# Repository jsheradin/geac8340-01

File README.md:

# geac8340-01
Modernization project for a library terminal keyboard

The libararies are not my own, I just referenced them. Only footprints I added are Stackpole and mounting holes.

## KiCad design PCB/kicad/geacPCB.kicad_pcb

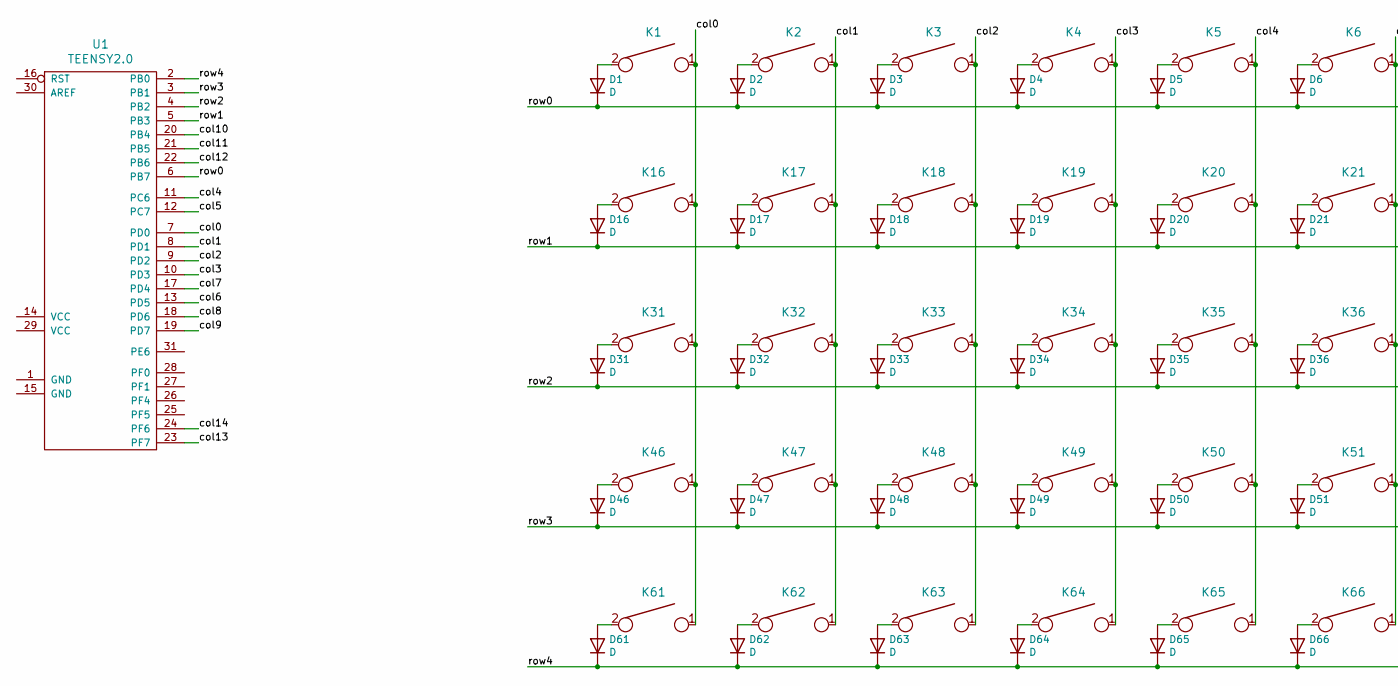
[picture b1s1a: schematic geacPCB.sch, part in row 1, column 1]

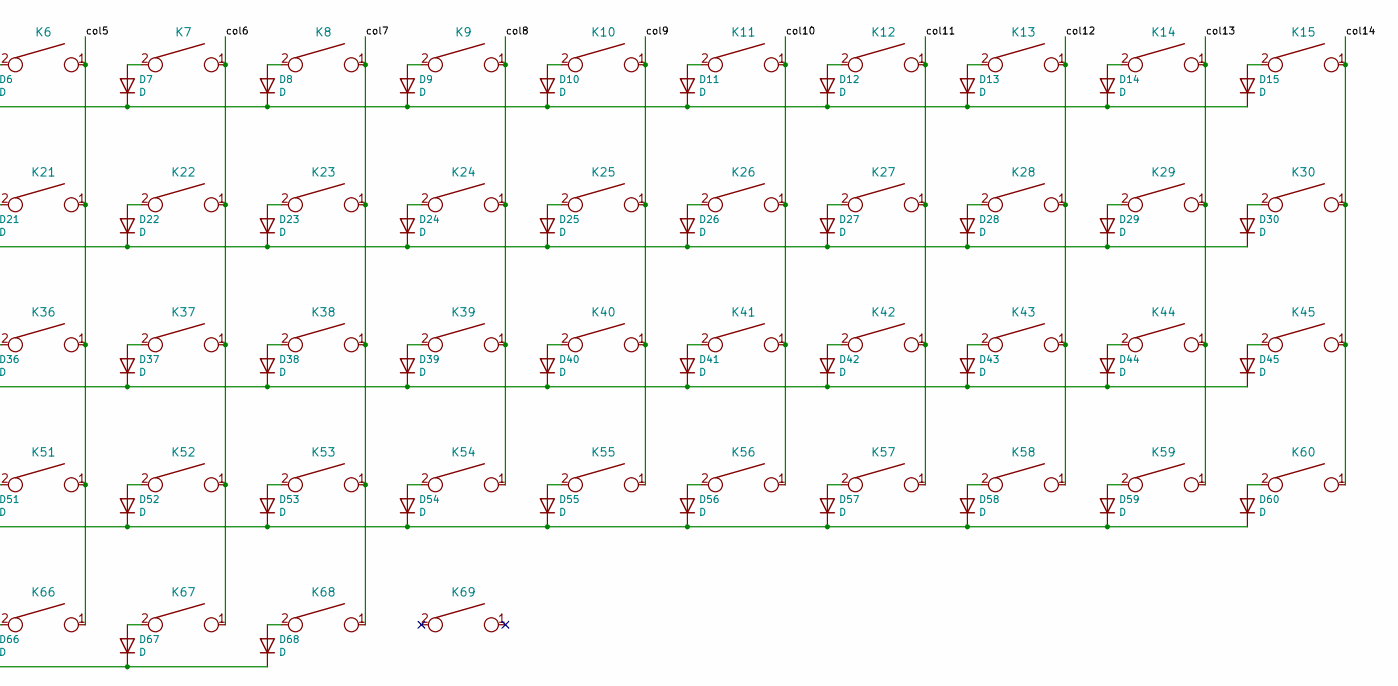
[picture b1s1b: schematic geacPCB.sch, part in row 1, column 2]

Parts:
D1, D2, D3, D4, D5, D6, D7, D8, D9, D10, D11, D12, D13, D14, D15, D16, D17, D18, D19, D20, D21, D22, D23, D24, D25, D26, D27, D28, D29, D30, D31, D32, D33, D34, D35, D36, D37, D38, D39, D40, D41, D42, D43, D44, D45, D46, D47, D48, D49, D50, D51, D52, D53, D54, D55, D56, D57, D58, D59, D60, D61, D62, D63, D64, D65, D66, D67, D68: D; D_SOD123_axial
K1, K2, K3, K4, K5, K6, K7, K8, K9, K10, K11, K12, K13, K14, K15, K16, K17, K18, K19, K20, K21, K22, K23, K24, K25, K26, K27, K28, K29, K30, K31, K32, K33, K34, K35, K36, K37, K38, K39, K40, K41, K42, K43, K44, K45, K46, K47, K48, K49, K50, K51, K52, K53, K54, K55, K56, K57, K58, K59, K60, K61, K62, K63, K64, K65, K66, K67, K68, K69: KEYSW; Stackpole
U1: TEENSY2.0; Teensy2.0

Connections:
/col0: K1.1, K16.1, K31.1, K46.1, K61.1, U1.7 (PD0)
/col1: K2.1, K17.1, K32.1, K47.1, K62.1, U1.8 (PD1)
/col2: K3.1, K18.1, K33.1, K48.1, K63.1, U1.9 (PD2)
/col3: K4.1, K19.1, K34.1, K49.1, K64.1, U1.10 (PD3)
/col4: K5.1, K20.1, K35.1, K50.1, K65.1, U1.11 (PC6)
/col5: K6.1, K21.1, K36.1, K51.1, K66.1, U1.12 (PC7)
/col6: K7.1, K22.1, K37.1, K52.1, K67.1, U1.13 (PD5)
/col7: K8.1, K23.1, K38.1, K53.1, K68.1, U1.17 (PD4)
/col8: K9.1, K24.1, K39.1, K54.1, U1.18 (PD6)
/col9: K10.1, K25.1, K40.1, K55.1, U1.19 (PD7)
/col10: K11.1, K26.1, K41.1, K56.1, U1.20 (PB4)
/col11: K12.1, K27.1, K42.1, K57.1, U1.21 (PB5)
/col12: K13.1, K28.1, K43.1, K58.1, U1.22 (PB6)
/col13: K14.1, K29.1, K44.1, K59.1, U1.23 (PF7)
/col14: K15.1, K30.1, K45.1, K60.1, U1.24 (PF6)
/row0: D1.1 (K), D2.1 (K), D3.1 (K), D4.1 (K), D5.1 (K), D6.1 (K), D7.1 (K), D8.1 (K), D9.1 (K), D10.1 (K), D11.1 (K), D12.1 (K), D13.1 (K), D14.1 (K), D15.1 (K), U1.6 (PB7)
/row1: D16.1 (K), D17.1 (K), D18.1 (K), D19.1 (K), D20.1 (K), D21.1 (K), D22.1 (K), D23.1 (K), D24.1 (K), D25.1 (K), D26.1 (K), D27.1 (K), D28.1 (K), D29.1 (K), D30.1 (K), U1.5 (PB3)
/row2: D31.1 (K), D32.1 (K), D33.1 (K), D34.1 (K), D35.1 (K), D36.1 (K), D37.1 (K), D38.1 (K), D39.1 (K), D40.1 (K), D41.1 (K), D42.1 (K), D43.1 (K), D44.1 (K), D45.1 (K), U1.4 (PB2)
/row3: D46.1 (K), D47.1 (K), D48.1 (K), D49.1 (K), D50.1 (K), D51.1 (K), D52.1 (K), D53.1 (K), D54.1 (K), D55.1 (K), D56.1 (K), D57.1 (K), D58.1 (K), D59.1 (K), D60.1 (K), U1.3 (PB1)
/row4: D61.1 (K), D62.1 (K), D63.1 (K), D64.1 (K), D65.1 (K), D66.1 (K), D67.1 (K), D68.1 (K), U1.2 (PB0)
unnamed: D1.2 (A), K1.2
unnamed: D2.2 (A), K2.2
unnamed: D3.2 (A), K3.2
unnamed: D4.2 (A), K4.2
unnamed: D5.2 (A), K5.2
unnamed: D6.2 (A), K6.2
unnamed: D7.2 (A), K7.2
unnamed: D8.2 (A), K8.2
unnamed: D9.2 (A), K9.2
unnamed: D10.2 (A), K10.2
unnamed: D11.2 (A), K11.2
unnamed: D12.2 (A), K12.2
unnamed: D13.2 (A), K13.2
unnamed: D14.2 (A), K14.2
unnamed: D15.2 (A), K15.2
unnamed: D16.2 (A), K16.2
unnamed: D17.2 (A), K17.2
unnamed: D18.2 (A), K18.2
unnamed: D19.2 (A), K19.2
unnamed: D20.2 (A), K20.2
unnamed: D21.2 (A), K21.2
unnamed: D22.2 (A), K22.2
unnamed: D23.2 (A), K23.2
unnamed: D24.2 (A), K24.2
unnamed: D25.2 (A), K25.2
unnamed: D26.2 (A), K26.2
unnamed: D27.2 (A), K27.2
unnamed: D28.2 (A), K28.2
unnamed: D29.2 (A), K29.2
unnamed: D30.2 (A), K30.2
unnamed: D31.2 (A), K31.2
unnamed: D32.2 (A), K32.2
unnamed: D33.2 (A), K33.2
unnamed: D34.2 (A), K34.2
unnamed: D35.2 (A), K35.2
unnamed: D36.2 (A), K36.2
unnamed: D37.2 (A), K37.2
unnamed: D38.2 (A), K38.2
unnamed: D39.2 (A), K39.2
unnamed: D40.2 (A), K40.2
unnamed: D41.2 (A), K41.2
unnamed: D42.2 (A), K42.2
unnamed: D43.2 (A), K43.2
unnamed: D44.2 (A), K44.2
unnamed: D45.2 (A), K45.2
unnamed: D46.2 (A), K46.2
unnamed: D47.2 (A), K47.2
unnamed: D48.2 (A), K48.2
unnamed: D49.2 (A), K49.2
unnamed: D50.2 (A), K50.2
unnamed: D51.2 (A), K51.2
unnamed: D52.2 (A), K52.2
unnamed: D53.2 (A), K53.2
unnamed: D54.2 (A), K54.2
unnamed: D55.2 (A), K55.2
unnamed: D56.2 (A), K56.2
unnamed: D57.2 (A), K57.2
unnamed: D58.2 (A), K58.2
unnamed: D59.2 (A), K59.2
unnamed: D60.2 (A), K60.2
unnamed: D61.2 (A), K61.2
unnamed: D62.2 (A), K62.2
unnamed: D63.2 (A), K63.2
unnamed: D64.2 (A), K64.2
unnamed: D65.2 (A), K65.2
unnamed: D66.2 (A), K66.2
unnamed: D67.2 (A), K67.2
unnamed: D68.2 (A), K68.2

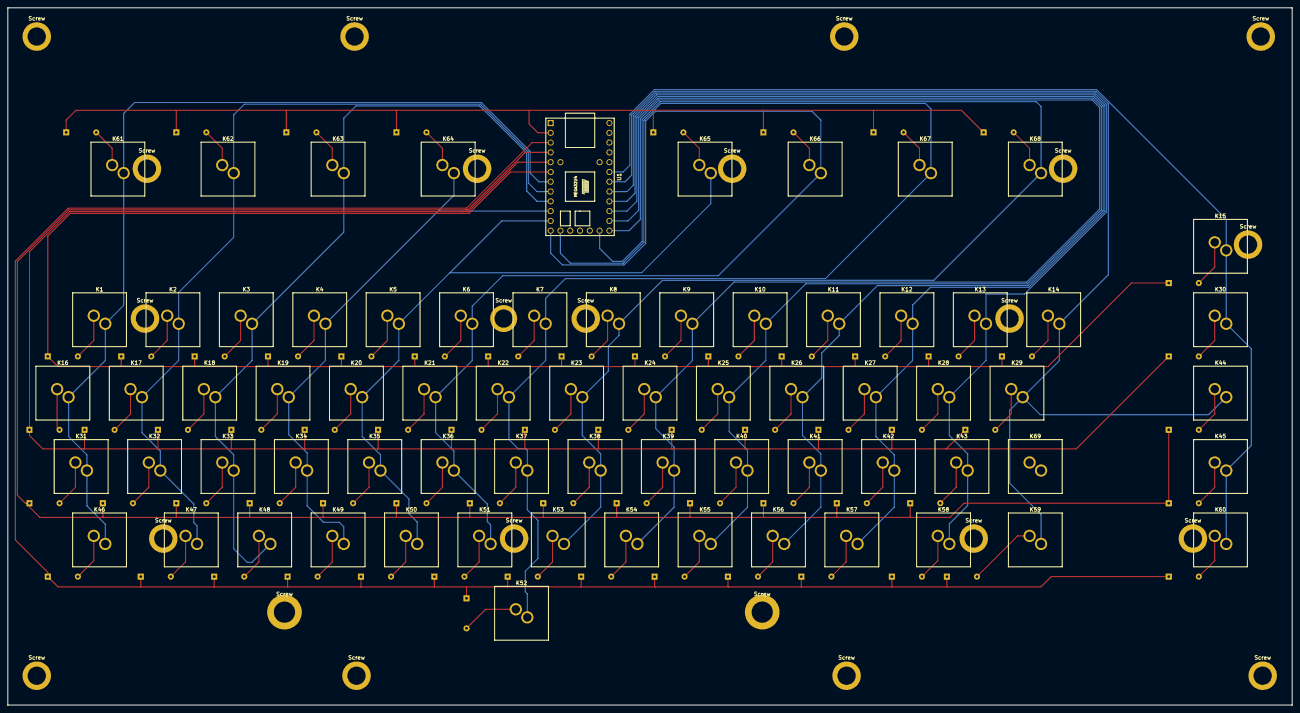
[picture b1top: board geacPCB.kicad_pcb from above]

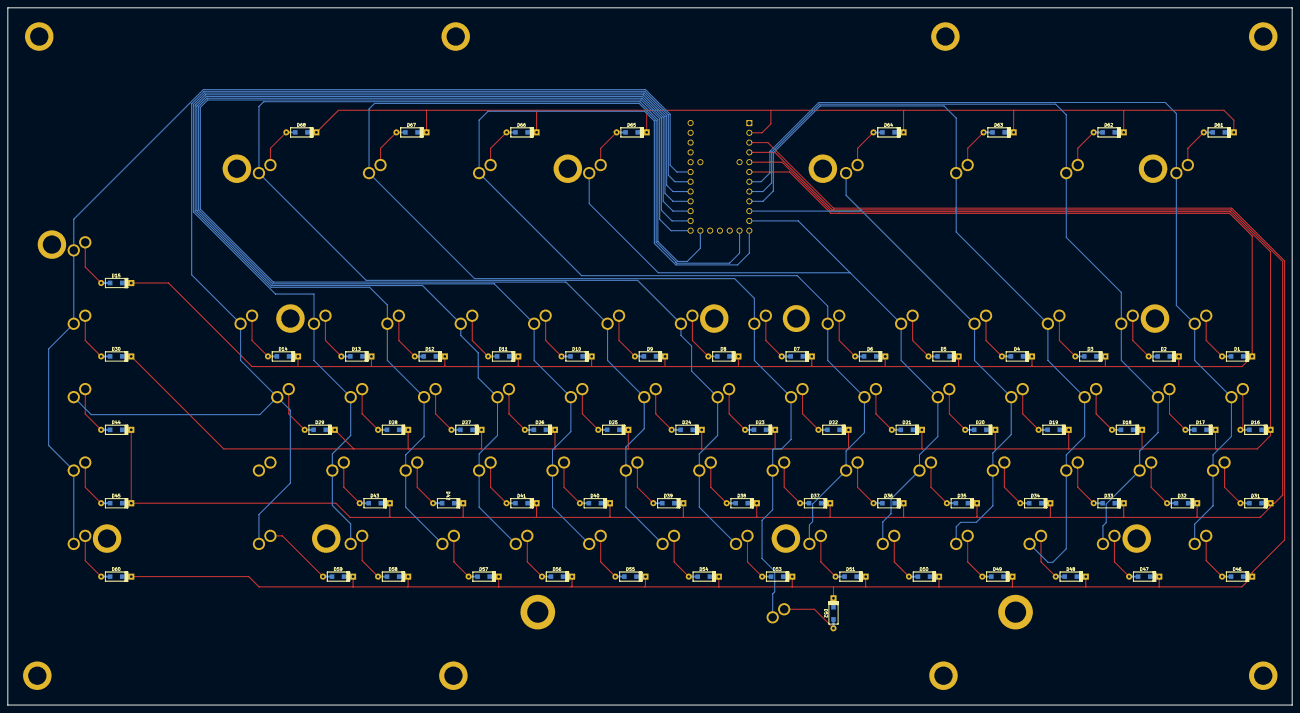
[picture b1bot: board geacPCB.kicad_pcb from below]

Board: 2 copper layers, 333.4 x 181.0 mm, 161 parts (68 on the bottom side), 88 nets.

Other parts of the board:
Screw: MountingHole_4.75mm
Screw#2, Screw#3: MountingHole_5.5mm
Screw#4, Screw#5, Screw#6, Screw#7, Screw#8, Screw#9, Screw#10, Screw#11, Screw#12, Screw#13, Screw#14, Screw#15, Screw#16, Screw#17, Screw#18, Screw#19, Screw#20, Screw#21, Screw#22, Screw#23: MountingHole_4.75mm

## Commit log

2021-01-01 Add KiCad project directory and libraries used
2021-01-12 Basic FW
